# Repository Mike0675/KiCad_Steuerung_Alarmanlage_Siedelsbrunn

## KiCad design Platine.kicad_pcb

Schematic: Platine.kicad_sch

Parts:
C1, C3, C5, C6, C7, C8: 100nF; C_0805_2012Metric_Pad1.18x1.45mm_HandSolder
C4: C; C_Disc_D3.0mm_W1.6mm_P2.50mm
C10, C11, C12: C_Polarized; CP_Radial_D6.3mm_P2.50mm
D1, D2, D3, D4, D5, D6, D7, D8, D9, D10, D11, D12, D13, D14, D15, D16, D17, D18, D19, D20, D21, D22, D23, D24, D25, D26, D27, D28, D29, D30, D31, D32, D33, D34, D35, D36, D37, D38, D39, D40, D42, D43, D44: LED; LED_D3.0mm
F1: 12V; Fuseholder_TR5_Littelfuse_No560_No460
F2: 5V; Fuseholder_TR5_Littelfuse_No560_No460
F3: 3.3V; Fuseholder_TR5_Littelfuse_No560_No460
J1: GND +12V; TerminalBlock_MetzConnect_Type166_1x02_P3.50mm_Horizontal
J2: Conn_01x09; PinSocket_1x9_P2.54mm_Vertical_SMD
J3: Display128x64_I2C; Display128x64_I2C_SMD
J4: +5V; TerminalBlock_MetzConnect_Type166_1x03_P3.50mm_Horizontal
J5: Serial 2; TerminalBlock_MetzConnect_Type059_RT06306HBWC_1x06_P3.50mm_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
J6: Serial 3; TerminalBlock_MetzConnect_Type059_RT06306HBWC_1x06_P3.50mm_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
J7, J8: Conn_01x24_Female; PinSocket_1x24_P2.54mm_Vertical_SMD
J9: Serial 4; TerminalBlock_MetzConnect_Type059_RT06306HBWC_1x06_P3.50mm_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
J10: RJ45_LED_Shielded; RJ45_Cetus_J1B1211CCD_Horizontal
J11: Serial 5; TerminalBlock_MetzConnect_Type059_RT06306HBWC_1x06_P3.50mm_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
J12: Serial 6; TerminalBlock_MetzConnect_Type059_RT06306HBWC_1x06_P3.50mm_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
J13: Serial 7; TerminalBlock_MetzConnect_Type059_RT06306HBWC_1x06_P3.50mm_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
J14: Serial 8; TerminalBlock_MetzConnect_Type059_RT06306HBWC_1x06_P3.50mm_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
J15: CAN 1; TerminalBlock_MetzConnect_Type059_RT06306HBWC_1x06_P3.50mm_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
J16, J17, J18, J19, J20, J21, J22, J23, J24, J25, J26, J27, J28, J29, J30, J31, J34, J35, J36, J37, J38, J39, J40, J41, J42, J43, J44, J45, J46, J47, J48, J49, J50, J51, J52, J53, J54, J55, J56, J57, J60, J61, J62, J63, J64, J65, J66, J67: Conn_01x02; TerminalBlock_MetzConnect_Type166_1x02_P3.50mm_Horizontal
J32, J58, J94: +12V; TerminalBlock_MetzConnect_Type166_1x03_P3.50mm_Horizontal
J33, J59, J77, J93, J95: GND; TerminalBlock_MetzConnect_Type166_1x03_P3.50mm_Horizontal
J68: Relais 1; TerminalBlock_MetzConnect_Type166_1x03_P3.50mm_Horizontal
J69: Relais 2; TerminalBlock_MetzConnect_Type166_1x03_P3.50mm_Horizontal
J70: Relais 3; TerminalBlock_MetzConnect_Type166_1x03_P3.50mm_Horizontal
J71: Relais 4; TerminalBlock_MetzConnect_Type166_1x03_P3.50mm_Horizontal
J72: Relais 5; TerminalBlock_MetzConnect_Type166_1x03_P3.50mm_Horizontal
J73: Relais 6; TerminalBlock_MetzConnect_Type166_1x03_P3.50mm_Horizontal
J74: Relais 7; TerminalBlock_MetzConnect_Type166_1x03_P3.50mm_Horizontal
J75: Relais 8; TerminalBlock_MetzConnect_Type166_1x03_P3.50mm_Horizontal
J76: +3.3V; TerminalBlock_MetzConnect_Type166_1x03_P3.50mm_Horizontal
J78: +3.3V; TerminalBlock_MetzConnect_Type166x1x05_P3.50mm_Horizontal
J79, J81, J90: GND; TerminalBlock_MetzConnect_Type166x1x05_P3.50mm_Horizontal
J80: +5V; TerminalBlock_MetzConnect_Type166x1x05_P3.50mm_Horizontal
J82: CAN-Module1; CAN_Pinsocket_SMD
J83: CAN-Module2; CAN_Pinsocket_SMD
J84: CAN 2; TerminalBlock_MetzConnect_Type059_RT06306HBWC_1x06_P3.50mm_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
J85: 1Wire; TerminalBlock_MetzConnect_Type166_1x03_P3.50mm_Horizontal
J86: SPI; SPI_Pinsocket_SMD
J87, J88, J97: Conn_01x02; PinHeader_1x02_P2.54mm_Vertical
J89: +12V; TerminalBlock_MetzConnect_Type166x1x05_P3.50mm_Horizontal
J91: Serial 1; TerminalBlock_MetzConnect_Type059_RT06306HBWC_1x06_P3.50mm_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
J92: Pullups´s; DIP-6_W7.62mm_SMD
J96: LoRa; LoRa_Pinsocket_SMD
K1, K2, K3, K4, K5, K6, K7, K8: FINDER-34.51; Relay_SPDT_Finder_34.51_Vertical
R1, R7: Endwiderst. CAN 120 Ohm; R_0603_1608Metric_Pad0.98x0.95mm_HandSolder
R3, R6: R_Small; R_0805_2012Metric_Pad1.20x1.40mm_HandSolder
R4, R5, R8: PULLUP; R_0805_2012Metric_Pad1.20x1.40mm_HandSolder
R9: 560 Ohm; R_0603_1608Metric_Pad0.98x0.95mm_HandSolder
R10: 68 Ohm; R_0603_1608Metric_Pad0.98x0.95mm_HandSolder
R11: 220 Ohm; R_0603_1608Metric_Pad0.98x0.95mm_HandSolder
RN1, RN2, RN3, RN4, RN5: R_Network08; PinSocket_1x9_P2.54mm_Vertical_SMD
SW1: Bildschirm AN; Ruwido Taster
U1: OKI-78SR-3.3_1.5-W36-C; Converter_DCDC_Murata_OKI-78SR_Vertical
U2: OKI-78SR-5_1.5-W36-C; Converter_DCDC_Murata_OKI-78SR_Vertical
U3: Teensy4.1; Teensy41_without_some_pins_SMD
U4, U6, U10: MCP23S17_SP; DIP-28_W7.62mm_SMD
U5, U8, U9, U12, U13: ULN2803A; DIP-18_W7.62mm_SMD
U7, U11: MCP23017_SP; DIP-28_W7.62mm_SMD

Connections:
1Wire: J7.11, J85.1, J92.4, U3.11 (9_OUT1C)
+3.3V: C1.1, C5.1, C6.1, C7.1, C8.1, F3.1, J3.1, J5.5, J6.5, J9.5, J11.5, J12.5, J13.5, J14.5, J15.5, J76.1, J76.2, J76.3, J78.1, J78.2, J78.3, J78.4, J78.5, J82.1, J83.1, J84.5, J85.2, J86.4, J91.5, J92.1, J92.2, J92.3, J96.4, J97.2, R3.1, R4.1, R5.1, R6.1, R8.1, R10.2, U4.9 (VDD), U4.15 (A0), U4.16 (A1), U4.17 (A2), U6.9 (VDD), U6.16 (A1), U7.9 (VDD), U10.9 (VDD), U10.15 (A0), U10.16 (A1), U11.9 (VDD), U11.15 (A0)
+5V: C3.1, F2.1, J4.1, J4.2, J4.3, J5.4, J6.4, J8.1, J9.4, J11.4, J12.4, J13.4, J14.4, J15.4, J80.1, J80.2, J80.3, J80.4, J80.5, J84.4, J86.3, J91.4, R11.2, U3.48 (VIN)
+12V: C10.1, F1.2, J1.2, U2.1 (IN)
+12V.1: F1.1, J5.3, J6.3, J9.3, J11.3, J12.3, J13.3, J14.3, J15.3, J32.1, J32.2, J32.3, J58.1, J58.2, J58.3, J84.3, J86.1, J89.1, J89.2, J89.3, J89.4, J89.5, J91.3, J94.1, J94.2, J94.3, K1.A2, K2.A2, K3.A2, K4.A2, K5.A2, K6.A2, K7.A2, K8.A2, R9.2, RN1.1 (common), RN2.1 (common), RN3.1 (common), RN4.1 (common), RN5.1 (common), U5.10 (COM), U8.10 (COM), U9.10 (COM), U12.10 (COM), U13.10 (COM)
CAN1_RX: J8.4, J82.4, U3.45 (23_A9_CRX1_MCLK1)
CAN1_TX: J8.5, J82.3, U3.44 (22_A8_CTX1)
CAN2_RX: J7.22, J83.4, U3.22 (30_CRX3)
CAN2_TX: J7.23, J83.3, U3.23 (31_CTX3)
GND: C1.2, C3.2, C5.2, C6.2, C7.2, C8.2, C10.2, C11.2, C12.2, D42.1 (K), D43.1 (K), D44.1 (K), J1.1, J2.9, J3.2, J5.6, J6.6, J7.1, J8.2, J8.15, J9.6, J10.13, J11.6, J12.6, J13.6, J14.6, J15.6, J16.2, J17.2, J18.2, J19.2, J20.2, J21.2, J22.2, J23.2, J24.2, J25.2, J26.2, J27.2, J28.2, J29.2, J30.2, J31.2, J33.1, J33.2, J33.3, J42.2, J43.2, J44.2, J45.2, J46.2, J47.2, J48.2, J49.2, J50.2, J51.2, J52.2, J53.2, J54.2, J55.2, J56.2, J57.2, J59.1, J59.2, J59.3, J77.1, J77.2, J77.3, J79.1, J79.2, J79.3, J79.4, J79.5, J81.1, J81.2, J81.3, J81.4, J81.5, J82.2, J83.2, J84.6, J85.3, J86.5, J90.1, J90.2, J90.3, J90.4, J90.5, J91.6, J93.1, J93.2, J93.3, J95.1, J95.2, J95.3, J96.5, SW1.2, U1.2 (GND), U2.2 (GND), U3.1 (GND), U3.34 (GND), U3.47 (GND), U3.52 (GND), U4.10 (VSS), U5.9 (GND), U6.10 (VSS), U6.15 (A0), U6.17 (A2), U7.10 (VSS), U7.15 (A0), U7.16 (A1), U7.17 (A2), U8.9 (GND), U9.9 (GND), U10.10 (VSS), U10.17 (A2), U11.10 (VSS), U11.16 (A1), U11.17 (A2), U12.9 (GND), U13.9 (GND)
LoRa_IRQ: J8.16, J96.3, U3.33 (41_A17)
LoRa_Reset: J8.17, J96.1, U3.32 (40_A16)
MCP0_INTA: J7.6, U3.6 (4_BCLK2), U7.20 (INTA)
MCP0_INTB: J7.5, U3.5 (3_LRCLK2), U7.19 (INTB)
MCP1_INTA: J7.7, U3.7 (5_IN2), U11.20 (INTA)
MCP1_INTB: J7.8, U3.8 (6_OUT1D), U11.19 (INTB)
unnamed: C4.1, J10.8, J10.9, U3.64 (GND)
unnamed: C4.2, J10.2, J10.5
unnamed: D1.2 (A), RN1.2 (R1)
unnamed: D1.1 (K), J34.1, U5.18 (O1)
unnamed: D2.2 (A), RN1.3 (R2)
unnamed: D2.1 (K), J34.2, U5.17 (O2)
unnamed: D3.2 (A), RN1.4 (R3)
unnamed: D3.1 (K), J35.1, U5.16 (O3)
unnamed: D4.2 (A), RN1.5 (R4)
unnamed: D4.1 (K), J35.2, U5.15 (O4)
unnamed: D5.2 (A), RN1.6 (R5)
unnamed: D5.1 (K), J36.1, U5.14 (O5)
unnamed: D6.2 (A), RN1.7 (R6)
unnamed: D6.1 (K), J36.2, U5.13 (O6)
unnamed: D7.2 (A), RN1.8 (R7)
unnamed: D7.1 (K), J37.1, U5.12 (O7)
unnamed: D8.2 (A), RN1.9 (R8)
unnamed: D8.1 (K), J37.2, U5.11 (O8)
unnamed: D9.2 (A), RN2.2 (R1)
unnamed: D9.1 (K), J38.1, U8.18 (O1)
unnamed: D10.2 (A), RN2.3 (R2)
unnamed: D10.1 (K), J38.2, U8.17 (O2)
unnamed: D11.2 (A), RN2.4 (R3)
unnamed: D11.1 (K), J39.1, U8.16 (O3)
unnamed: D12.2 (A), RN2.5 (R4)
unnamed: D12.1 (K), J39.2, U8.15 (O4)
unnamed: D13.2 (A), RN2.6 (R5)
unnamed: D13.1 (K), J40.1, U8.14 (O5)
unnamed: D14.2 (A), RN2.7 (R6)
unnamed: D14.1 (K), J40.2, U8.13 (O6)
unnamed: D15.2 (A), RN2.8 (R7)
unnamed: D15.1 (K), J41.1, U8.12 (O7)
unnamed: D16.2 (A), RN2.9 (R8)
unnamed: D16.1 (K), J41.2, U8.11 (O8)
unnamed: D17.2 (A), RN3.2 (R1)
unnamed: D17.1 (K), J60.1, U9.18 (O1)
unnamed: D18.2 (A), RN3.3 (R2)
unnamed: D18.1 (K), J60.2, U9.17 (O2)
unnamed: D19.2 (A), RN3.4 (R3)
unnamed: D19.1 (K), J61.1, U9.16 (O3)
unnamed: D20.2 (A), RN3.5 (R4)
unnamed: D20.1 (K), J61.2, U9.15 (O4)
unnamed: D21.2 (A), RN3.6 (R5)
unnamed: D21.1 (K), J62.1, U9.14 (O5)
unnamed: D22.2 (A), RN3.7 (R6)
unnamed: D22.1 (K), J62.2, U9.13 (O6)
unnamed: D23.2 (A), RN3.8 (R7)
unnamed: D23.1 (K), J63.1, U9.12 (O7)
unnamed: D24.2 (A), RN3.9 (R8)
unnamed: D24.1 (K), J63.2, U9.11 (O8)
unnamed: D25.2 (A), RN4.2 (R1)
unnamed: D25.1 (K), J64.1, U12.18 (O1)
unnamed: D26.2 (A), RN4.3 (R2)
unnamed: D26.1 (K), J64.2, U12.17 (O2)
unnamed: D27.2 (A), RN4.4 (R3)
unnamed: D27.1 (K), J65.1, U12.16 (O3)
unnamed: D28.2 (A), RN4.5 (R4)
unnamed: D28.1 (K), J65.2, U12.15 (O4)
unnamed: D29.2 (A), RN4.6 (R5)
unnamed: D29.1 (K), J66.1, U12.14 (O5)
unnamed: D30.2 (A), RN4.7 (R6)
unnamed: D30.1 (K), J66.2, U12.13 (O6)
unnamed: D31.2 (A), RN4.8 (R7)
unnamed: D31.1 (K), J67.1, U12.12 (O7)
unnamed: D32.2 (A), RN4.9 (R8)
unnamed: D32.1 (K), J67.2, U12.11 (O8)
unnamed: D33.2 (A), RN5.2 (R1)
unnamed: D33.1 (K), K1.A1, U13.11 (O8)
unnamed: D34.2 (A), RN5.3 (R2)
unnamed: D34.1 (K), K2.A1, U13.12 (O7)
unnamed: D35.2 (A), RN5.4 (R3)
unnamed: D35.1 (K), K3.A1, U13.13 (O6)
unnamed: D36.2 (A), RN5.5 (R4)
unnamed: D36.1 (K), K4.A1, U13.14 (O5)
unnamed: D37.2 (A), RN5.6 (R5)
unnamed: D37.1 (K), K5.A1, U13.15 (O4)
unnamed: D38.2 (A), RN5.7 (R6)
unnamed: D38.1 (K), K6.A1, U13.16 (O3)
unnamed: D39.2 (A), RN5.8 (R7)
unnamed: D39.1 (K), K7.A1, U13.17 (O2)
unnamed: D40.2 (A), RN5.9 (R8)
unnamed: D40.1 (K), K8.A1, U13.18 (O1)
unnamed: D42.2 (A), R9.1
unnamed: D43.2 (A), R10.1
unnamed: D44.2 (A), R11.1
unnamed: J2.1, U4.21 (GPA0)
unnamed: J2.2, U4.22 (GPA1)
unnamed: J2.3, U4.23 (GPA2)
unnamed: J2.4, U4.24 (GPA3)
unnamed: J2.5, U4.25 (GPA4)
unnamed: J2.6, U4.26 (GPA5)
unnamed: J2.7, U4.27 (GPA6)
unnamed: J2.8, U4.28 (GPA7)
unnamed: J7.15, U3.15 (3V3)
unnamed: J7.24, U3.24 (32_OUT1B)
unnamed: J8.3, J97.1, U3.46 (3V3)
unnamed: J8.14, U3.35 (13_SCK_LED)
unnamed: J8.21, U3.28 (36_CS)
unnamed: J15.1, J82.5, R1.2
unnamed: J15.2, J82.6, J87.1
unnamed: J16.1, U7.1 (GPB0)
unnamed: J17.1, U7.2 (GPB1)
unnamed: J18.1, U7.3 (GPB2)
unnamed: J19.1, U7.4 (GPB3)
unnamed: J20.1, U7.5 (GPB4)
unnamed: J21.1, U7.6 (GPB5)
unnamed: J22.1, U7.7 (GPB6)
unnamed: J23.1, U7.8 (GPB7)
unnamed: J24.1, U7.21 (GPA0)
unnamed: J25.1, U7.22 (GPA1)
unnamed: J26.1, U7.23 (GPA2)
unnamed: J27.1, U7.24 (GPA3)
unnamed: J28.1, U7.25 (GPA4)
unnamed: J29.1, U7.26 (GPA5)
unnamed: J30.1, U7.27 (GPA6)
unnamed: J31.1, U7.28 (GPA7)
unnamed: J42.1, U11.1 (GPB0)
unnamed: J43.1, U11.2 (GPB1)
unnamed: J44.1, U11.3 (GPB2)
unnamed: J45.1, U11.4 (GPB3)
unnamed: J46.1, U11.5 (GPB4)
unnamed: J47.1, U11.6 (GPB5)
unnamed: J48.1, U11.7 (GPB6)
unnamed: J49.1, U11.8 (GPB7)
unnamed: J50.1, U11.21 (GPA0)
unnamed: J51.1, U11.22 (GPA1)
unnamed: J52.1, U11.23 (GPA2)
unnamed: J53.1, U11.24 (GPA3)
unnamed: J54.1, U11.25 (GPA4)
unnamed: J55.1, U11.26 (GPA5)
unnamed: J56.1, U11.27 (GPA6)
unnamed: J57.1, U11.28 (GPA7)
unnamed: J68.1, K1.14
unnamed: J68.2, K1.11
unnamed: J68.3, K1.12
unnamed: J69.1, K2.14
unnamed: J69.2, K2.11
unnamed: J69.3, K2.12
unnamed: J70.1, K3.14
unnamed: J70.2, K3.11
unnamed: J70.3, K3.12
unnamed: J71.1, K4.14
unnamed: J71.2, K4.11
unnamed: J71.3, K4.12
unnamed: J72.1, K5.14
unnamed: J72.2, K5.11
unnamed: J72.3, K5.12
unnamed: J73.1, K6.14
unnamed: J73.2, K6.11
unnamed: J73.3, K6.12
unnamed: J74.1, K7.14
unnamed: J74.2, K7.11
unnamed: J74.3, K7.12
unnamed: J75.1, K8.14
unnamed: J75.2, K8.11
unnamed: J75.3, K8.12
unnamed: J83.5, J84.1, R7.2
unnamed: J83.6, J84.2, J88.1
unnamed: J87.2, R1.1
unnamed: J88.2, R7.1
unnamed: C11.1, F2.2, U1.1 (IN), U2.3 (OUT)
unnamed: C12.1, F3.2, U1.3 (OUT)
unnamed: J10.10, U3.61 (LED)
unnamed: J10.4, U3.60 (R+)
unnamed: J10.6, U3.65 (R-)
unnamed: J10.1, U3.63 (T+)
unnamed: J10.3, U3.62 (T-)
unnamed: R8.2, U4.18 (~RESET)
unnamed: U5.1 (I1), U6.1 (GPB0)
unnamed: U5.2 (I2), U6.2 (GPB1)
unnamed: U5.3 (I3), U6.3 (GPB2)
unnamed: U5.4 (I4), U6.4 (GPB3)
unnamed: U5.5 (I5), U6.5 (GPB4)
unnamed: U5.6 (I6), U6.6 (GPB5)
unnamed: U5.7 (I7), U6.7 (GPB6)
unnamed: U5.8 (I8), U6.8 (GPB7)
unnamed: U6.21 (GPA0), U8.1 (I1)
unnamed: U6.22 (GPA1), U8.2 (I2)
unnamed: U6.23 (GPA2), U8.3 (I3)
unnamed: U6.24 (GPA3), U8.4 (I4)
unnamed: U6.25 (GPA4), U8.5 (I5)
unnamed: U6.26 (GPA5), U8.6 (I6)
unnamed: U6.27 (GPA6), U8.7 (I7)
unnamed: U6.28 (GPA7), U8.8 (I8)
unnamed: R4.2, U6.18 (~RESET)
unnamed: R3.2, U7.18 (~RESET)
unnamed: U10.21 (GPA0), U12.1 (I1)
unnamed: U10.22 (GPA1), U12.2 (I2)
unnamed: U10.23 (GPA2), U12.3 (I3)
unnamed: U10.24 (GPA3), U12.4 (I4)
unnamed: U10.25 (GPA4), U12.5 (I5)
unnamed: U10.26 (GPA5), U12.6 (I6)
unnamed: U10.27 (GPA6), U12.7 (I7)
unnamed: U10.28 (GPA7), U12.8 (I8)
unnamed: U9.1 (I1), U10.1 (GPB0)
unnamed: U9.2 (I2), U10.2 (GPB1)
unnamed: U9.3 (I3), U10.3 (GPB2)
unnamed: U9.4 (I4), U10.4 (GPB3)
unnamed: U9.5 (I5), U10.5 (GPB4)
unnamed: U9.6 (I6), U10.6 (GPB5)
unnamed: U9.7 (I7), U10.7 (GPB6)
unnamed: U9.8 (I8), U10.8 (GPB7)
unnamed: R5.2, U10.18 (~RESET)
unnamed: R6.2, U11.18 (~RESET)
unnamed: U4.8 (GPB7), U13.1 (I1)
unnamed: U4.7 (GPB6), U13.2 (I2)
unnamed: U4.6 (GPB5), U13.3 (I3)
unnamed: U4.5 (GPB4), U13.4 (I4)
unnamed: U4.4 (GPB3), U13.5 (I5)
unnamed: U4.3 (GPB2), U13.6 (I6)
unnamed: U4.2 (GPB1), U13.7 (I7)
unnamed: U4.1 (GPB0), U13.8 (I8)
RX1: J7.2, J91.1, U3.2 (0_RX1_CRX2_CS1)
RX2: J5.1, J7.9, U3.9 (7_RX2_OUT1A)
RX3: J6.1, J8.12, U3.37 (15_A1_RX3_SPDIF_IN)
RX4: J8.11, J9.1, U3.38 (16_A2_RX4_SCL1)
RX5: J8.6, J11.1, U3.43 (21_A7_RX5_BCLK1)
RX6: J7.17, J12.1, U3.17 (25_A11_RX6_SDA2)
RX7: J7.20, J13.1, U3.20 (28_RX7)
RX8: J8.23, J14.1, U3.26 (34_RX8)
Relais1: J8.24, U3.25 (33_MCLK2)
SCL: J3.3, J8.8, J92.6, U3.41 (19_A5_SCL), U4.12 (SCK), U6.12 (SCK), U7.12 (SCK), U10.12 (SCK), U11.12 (SCK)
SDA: J3.4, J8.9, J92.5, U3.40 (18_A4_SDA), U4.13 (SDA), U6.13 (SDA), U7.13 (SDA), U10.13 (SDA), U11.13 (SDA)
SPI_CS: J7.12, J86.6, U3.12 (10_CS_MQSR)
SPI_CS1: J8.19, J96.6, U3.30 (38_CS1_IN1)
SPI_MISO: J7.14, J86.8, U3.14 (12_MISO_MQSL)
SPI_MISO1: J8.18, J96.9, U3.31 (39_MISO1_OUT1A)
SPI_MOSI: J7.13, J86.7, U3.13 (11_MOSI_CTX1)
SPI_MOSI1: J7.18, J96.8, U3.18 (26_A12_MOSI1)
SPI_SCK: J8.20, J86.9, U3.29 (37_CS)
SPI_SCK1: J7.19, J96.7, U3.19 (27_A13_SCK1)
TX1: J7.3, J91.2, U3.3 (1_TX1_CTX2_MISO1)
TX2: J5.2, J7.10, U3.10 (8_TX2_IN1)
TX3: J6.2, J8.13, U3.36 (14_A0_TX3_SPDIF_OUT)
TX4: J8.10, J9.2, U3.39 (17_A3_TX4_SDA1)
TX5: J8.7, J11.2, U3.42 (20_A6_TX5_LRCLK1)
TX6: J7.16, J12.2, U3.16 (24_A10_TX6_SCL2)
TX7: J7.21, J13.2, U3.21 (29_TX7)
TX8: J8.22, J14.2, U3.27 (35_TX8)
Taster: J7.4, SW1.1, U3.4 (2_OUT2)

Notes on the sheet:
100
110
010
111
000

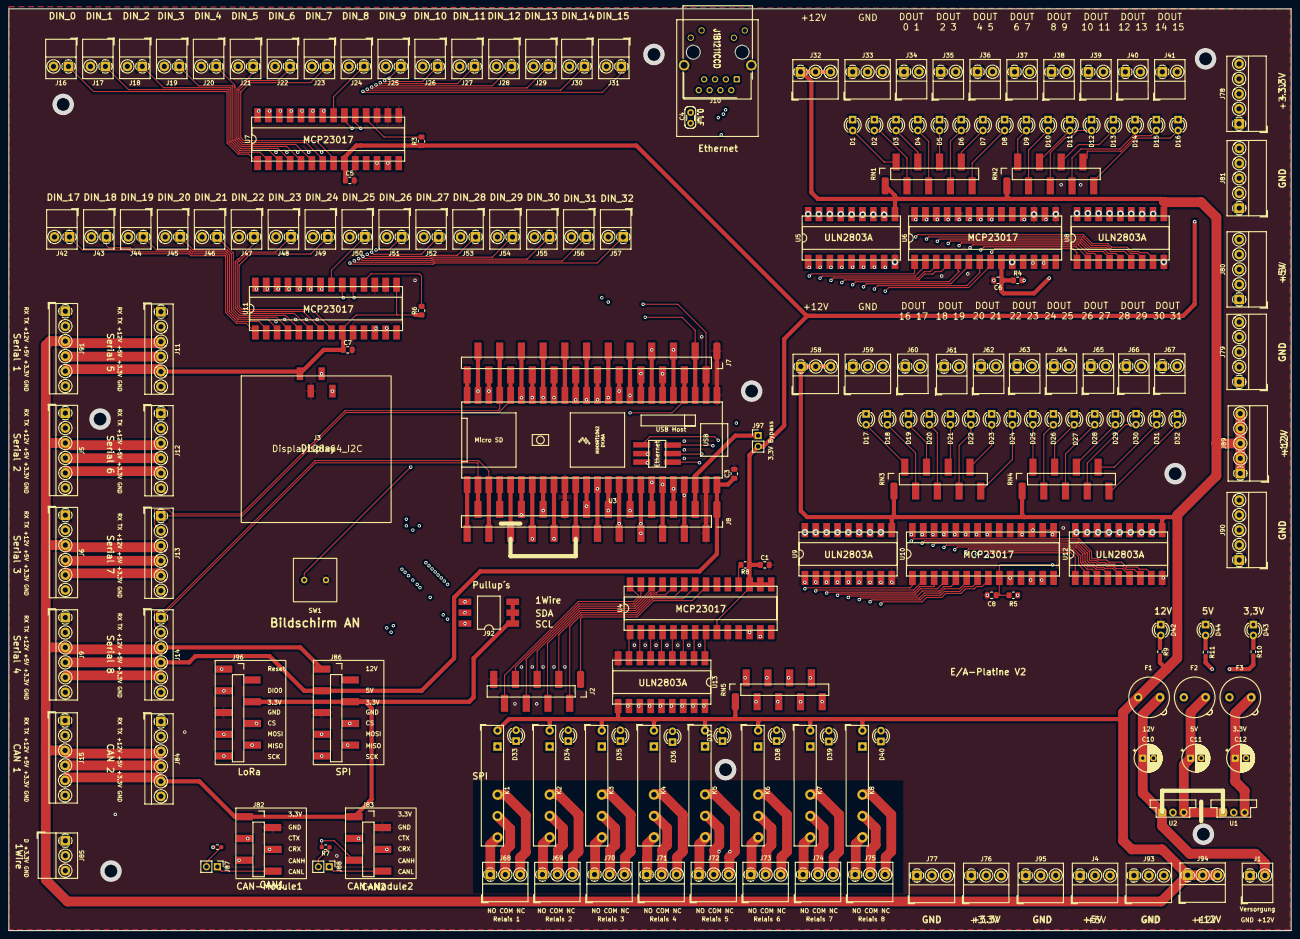
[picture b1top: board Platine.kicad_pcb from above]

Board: 4 copper layers, 299.9 x 215.6 mm, 190 parts (0 on the bottom side), 256 nets.
